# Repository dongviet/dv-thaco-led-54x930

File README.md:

## LED 54X930

## YÊU CẦU DỰ ÁN

	- Dimension		:54x930
	- LED			:smd5050
	- Số lượng LED	:64 LED

## MẠCH NGUYÊN LÝ

## MẠCH PCB

## MẠCH 3D

## FILM_POS

## FILM_NEG

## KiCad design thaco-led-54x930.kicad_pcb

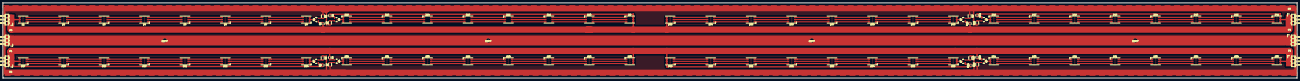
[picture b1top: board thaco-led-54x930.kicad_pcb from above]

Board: 2 copper layers, 930.0 x 54.0 mm, 94 parts (0 on the bottom side), 195 nets.

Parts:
D1, D2, D3: LED; LED_WS2812-PLCC6
D4, D5, D6, D7, D8, D9, D10, D11, D12, D13, D14, D15, D16, D17, D18, D19, D20, D21, D22, D23, D24, D25, D26, D27, D28, D29, D30, D31, D32, D33, D34, D35, D36, D37, D38, D39, D40, D41, D42, D43, D44, D45, D46, D47, D48, D49, D50, D51, D52, D53, D54, D55, D56, D57, D58, D59, D60, D61, D62, D63, D64: LED_RGB; LED_WS2812-PLCC6
P1, P5, P6: CONN_01X03; Pin_Header_Angled_1x03
P2, P3, P4: Pin_Header_Angled_1x03
Q1, Q2, Q3, Q4, Q5, Q6, Q7, Q8: SOT-23
R1, R3, R5, R7, R9, R11, R13, R15: R_1206
R2, R4, R6, R8, R10, R12, R14, R16: R_0805

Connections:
GND: P1.1, P1.2, P1.3, P4.1, P4.2, P4.3, R1.1, R3.1, R5.1, R7.1, R9.1, R11.1, R13.1, R15.1
J1: D1.4, D1.5, D1.6, D9.4, D9.5, D9.6, D33.4, D33.5, D33.6, D41.4, D41.5, D41.6, P3.1, P3.2, P3.3, P6.1, P6.2, P6.3, R2.1, R4.1, R10.1, R12.1
J2: D17.4, D17.5, D17.6, D25.4, D25.5, D25.6, D49.4, D49.5, D49.6, D57.4, D57.5, D57.6, P2.1, P2.2, P2.3, P5.1, P5.2, P5.3, R6.1, R8.1, R14.1, R16.1
unnamed: D1.1, D2.6
unnamed: D1.2, D2.5
unnamed: D1.3, D2.4
unnamed: D2.1, D3.6
unnamed: D2.2, D3.5
unnamed: D2.3, D3.4
unnamed: D3.1, D4.6
unnamed: D3.2, D4.5
unnamed: D3.3, D4.4
unnamed: D4.1, D5.6
unnamed: D4.2, D5.5
unnamed: D4.3, D5.4
unnamed: D5.1, D6.6
unnamed: D5.2, D6.5
unnamed: D5.3, D6.4
unnamed: D6.1, D7.6
unnamed: D6.2, D7.5
unnamed: D6.3, D7.4
unnamed: D7.1, D8.6
unnamed: D7.2, D8.5
unnamed: D7.3, D8.4
unnamed: D8.1, D8.2, D8.3, Q1.3
unnamed: D10.1, D11.6
unnamed: D10.2, D11.5
unnamed: D10.3, D11.4
unnamed: D9.3, D10.4
unnamed: D9.2, D10.5
unnamed: D9.1, D10.6
unnamed: D11.1, D12.6
unnamed: D11.2, D12.5
unnamed: D11.3, D12.4
unnamed: D12.1, D13.6
unnamed: D12.2, D13.5
unnamed: D12.3, D13.4
unnamed: D13.1, D14.6
unnamed: D13.2, D14.5
unnamed: D13.3, D14.4
unnamed: D14.1, D15.6
unnamed: D14.2, D15.5
unnamed: D14.3, D15.4
unnamed: D15.1, D16.6
unnamed: D15.2, D16.5
unnamed: D15.3, D16.4
unnamed: D16.1, D16.2, D16.3, Q2.3
unnamed: D17.1, D18.6
unnamed: D17.2, D18.5
unnamed: D17.3, D18.4
unnamed: D18.1, D19.6
unnamed: D18.2, D19.5
unnamed: D18.3, D19.4
unnamed: D19.1, D20.6
unnamed: D19.2, D20.5
unnamed: D19.3, D20.4
unnamed: D20.1, D21.6
unnamed: D20.2, D21.5
unnamed: D20.3, D21.4
unnamed: D21.1, D22.6
unnamed: D21.2, D22.5
unnamed: D21.3, D22.4
unnamed: D22.1, D23.6
unnamed: D22.2, D23.5
unnamed: D22.3, D23.4
unnamed: D23.1, D24.6
unnamed: D23.2, D24.5
unnamed: D23.3, D24.4
unnamed: D24.1, D24.2, D24.3, Q3.3
unnamed: D25.1, D26.6
unnamed: D25.2, D26.5
unnamed: D25.3, D26.4
unnamed: D26.1, D27.6
unnamed: D26.2, D27.5
unnamed: D26.3, D27.4
unnamed: D27.1, D28.6
unnamed: D27.2, D28.5
unnamed: D27.3, D28.4
unnamed: D28.1, D29.6
unnamed: D28.2, D29.5
unnamed: D28.3, D29.4
unnamed: D29.1, D30.6
unnamed: D29.2, D30.5
unnamed: D29.3, D30.4
unnamed: D30.1, D31.6
unnamed: D30.2, D31.5
unnamed: D30.3, D31.4
unnamed: D31.1, D32.6
unnamed: D31.2, D32.5
unnamed: D31.3, D32.4
unnamed: D32.1, D32.2, D32.3, Q4.3
unnamed: D33.1, D34.6
unnamed: D33.2, D34.5
unnamed: D33.3, D34.4
unnamed: D34.1, D35.6
unnamed: D34.2, D35.5
unnamed: D34.3, D35.4
unnamed: D35.1, D36.6
unnamed: D35.2, D36.5
unnamed: D35.3, D36.4
unnamed: D36.1, D37.6
unnamed: D36.2, D37.5
unnamed: D36.3, D37.4
unnamed: D37.1, D38.6
unnamed: D37.2, D38.5
unnamed: D37.3, D38.4
unnamed: D38.1, D39.6
unnamed: D38.2, D39.5
unnamed: D38.3, D39.4
unnamed: D39.1, D40.6
unnamed: D39.2, D40.5
unnamed: D39.3, D40.4
unnamed: D40.1, D40.2, D40.3, Q5.3
unnamed: D41.1, D42.6
unnamed: D41.2, D42.5
unnamed: D41.3, D42.4
unnamed: D42.1, D43.6
unnamed: D42.2, D43.5
unnamed: D42.3, D43.4
unnamed: D43.1, D44.6
unnamed: D43.2, D44.5
unnamed: D43.3, D44.4
unnamed: D44.1, D45.6
unnamed: D44.2, D45.5
unnamed: D44.3, D45.4
unnamed: D45.1, D46.6
unnamed: D45.2, D46.5
unnamed: D45.3, D46.4
unnamed: D46.1, D47.6
unnamed: D46.2, D47.5
unnamed: D46.3, D47.4
unnamed: D47.1, D48.6
unnamed: D47.2, D48.5
unnamed: D47.3, D48.4
unnamed: D48.1, D48.2, D48.3, Q6.3
unnamed: D49.1, D50.6
unnamed: D49.2, D50.5
unnamed: D49.3, D50.4
unnamed: D50.1, D51.6
unnamed: D50.2, D51.5
unnamed: D50.3, D51.4
unnamed: D51.1, D52.6
unnamed: D51.2, D52.5
unnamed: D51.3, D52.4
unnamed: D52.1, D53.6
unnamed: D52.2, D53.5
unnamed: D52.3, D53.4
unnamed: D53.1, D54.6
unnamed: D53.2, D54.5
unnamed: D53.3, D54.4
unnamed: D54.1, D55.6
unnamed: D54.2, D55.5
unnamed: D54.3, D55.4
unnamed: D55.1, D56.6
unnamed: D55.2, D56.5
unnamed: D55.3, D56.4
unnamed: D56.1, D56.2, D56.3, Q7.3
unnamed: D57.1, D58.6
unnamed: D57.2, D58.5
unnamed: D57.3, D58.4
unnamed: D58.1, D59.6
unnamed: D58.2, D59.5
unnamed: D58.3, D59.4
unnamed: D59.1, D60.6
unnamed: D59.2, D60.5
unnamed: D59.3, D60.4
unnamed: D60.1, D61.6
unnamed: D60.2, D61.5
unnamed: D60.3, D61.4
unnamed: D61.1, D62.6
unnamed: D61.2, D62.5
unnamed: D61.3, D62.4
unnamed: D62.1, D63.6
unnamed: D62.2, D63.5
unnamed: D62.3, D63.4
unnamed: D63.1, D64.6
unnamed: D63.2, D64.5
unnamed: D63.3, D64.4
unnamed: D64.1, D64.2, D64.3, Q8.3
unnamed: Q1.1, R2.2
unnamed: Q1.2, R1.2
unnamed: Q2.1, R4.2
unnamed: Q2.2, R3.2
unnamed: Q3.1, R6.2
unnamed: Q3.2, R5.2
unnamed: Q4.1, R8.2
unnamed: Q4.2, R7.2
unnamed: Q5.1, R10.2
unnamed: Q5.2, R9.2
unnamed: Q6.1, R12.2
unnamed: Q6.2, R11.2
unnamed: Q7.1, R14.2
unnamed: Q7.2, R13.2
unnamed: Q8.1, R16.2
unnamed: Q8.2, R15.2

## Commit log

2016-06-28 add project
2016-06-28 initial
2016-06-29 project finish
2016-06-29 change file
